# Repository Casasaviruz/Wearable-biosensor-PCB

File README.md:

# Wearable-biosensor-PCB

A battery powered double sided PCB sensor meant to monitor the heart rate, breathing, temperature and sleep and active cycles of lab mice, made as small and non invasive as possible, data is transmitted through Bluetooth

Final Project — CSE 332 (Analog and Digital Circuits), DePaul University,
winter 2026.

# Specifications

- Dimensions: 27mm x 18mm
- Weight: ~ 3.05g (with battery)
- Microcontroller: nRF52832 (ARM Cortex-M4 + radio BLE)
- Sensors: MAX30101 (heart rate/ breathing), TMP117
  (temperature), LSM6DSL (accelerometer/gyroscope)

# Content 
`kicad/` - project files (pcb, schematics, libraries)
`report/` - complete technical report (component reasoning, calculations, simulation results)

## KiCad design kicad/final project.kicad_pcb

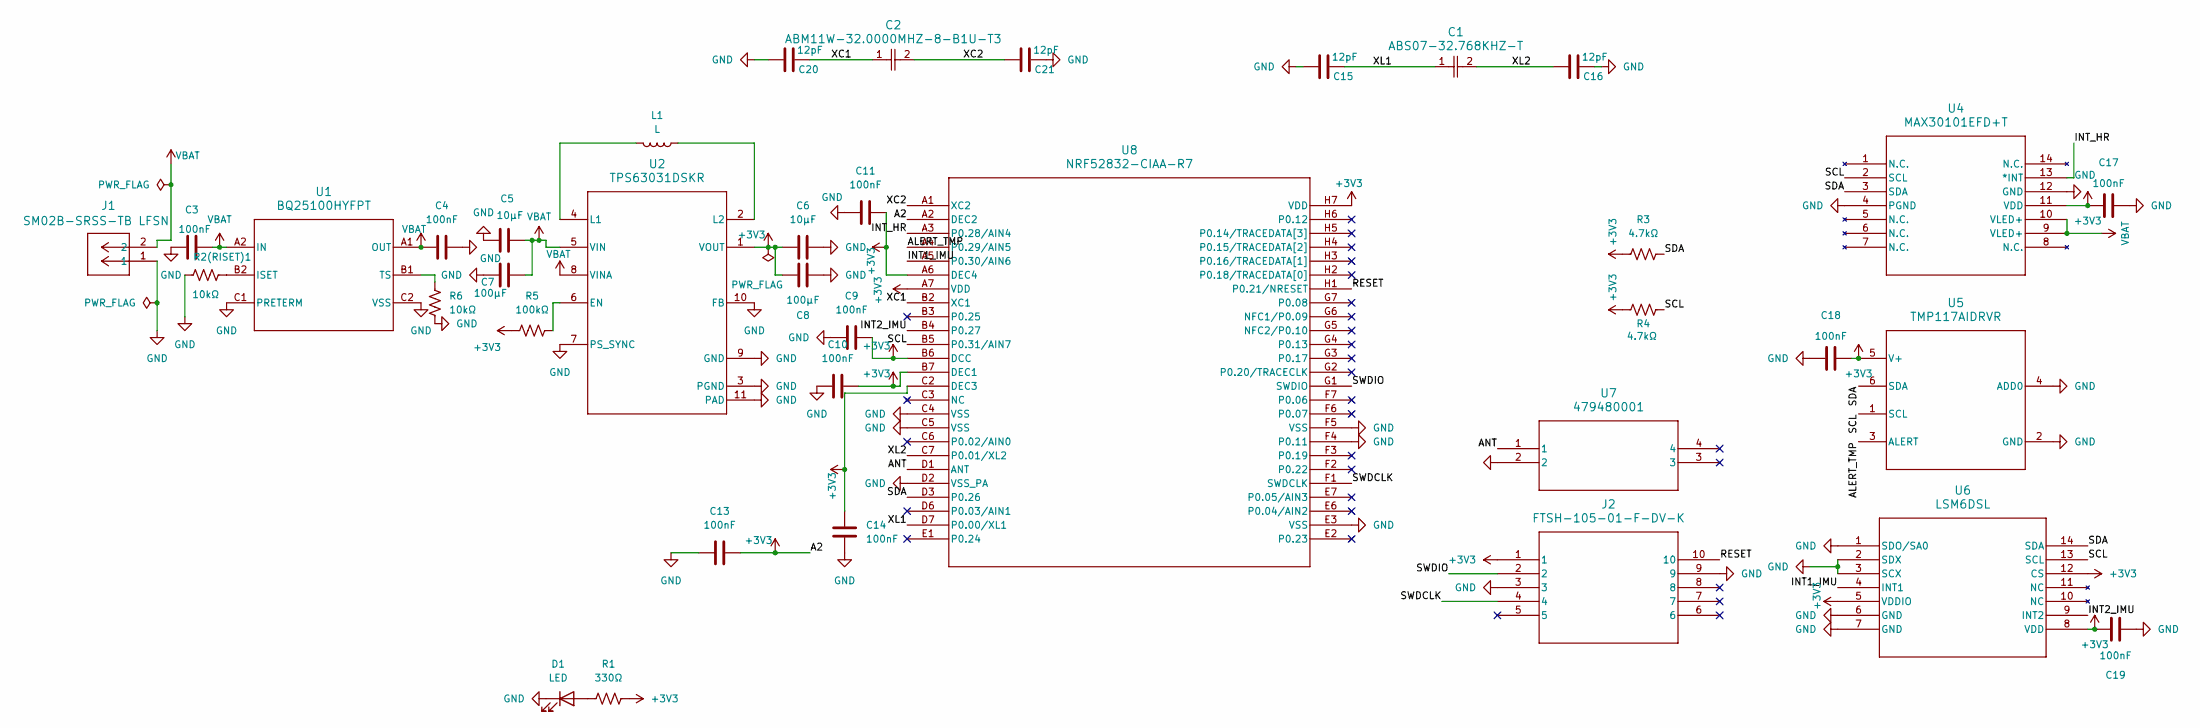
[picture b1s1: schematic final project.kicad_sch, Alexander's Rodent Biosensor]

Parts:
C1: ABS07-32.768KHZ-T; CAP_ABS07-32.768KHZ-T_ABR
C2: ABM11W-32.0000MHZ-8-B1U-T3; CAP_ABM11W-32.0000MHZ-8-B1U-T3_ABR
C3, C4, C9, C10, C11, C13, C14, C17, C18, C19: 100nF; C_0402_1005Metric
C5, C6: 10µF; C_0402_1005Metric
C7, C8: 100µF; C_0805_2012Metric
C15, C16, C20, C21: 12pF; C_0402_1005Metric
D1: LED; LED_0402_1005Metric
J1: SM02B-SRSS-TB LFSN; CONN_SM02B-SRSS-TB_JST
J2: FTSH-105-01-F-DV-K; FTSH-105-01-F-DV-K_SAI
L1: L; L_0402_1005Metric
R1: 330Ω; R_0402_1005Metric
R2(RISET)1, R6: 10kΩ; R_0402_1005Metric
R3, R4: 4.7kΩ; R_0402_1005Metric
R5: 100kΩ; R_0402_1005Metric
U1: BQ25100HYFPT; YFP0006AFAV
U2: TPS63031DSKR; DSK0010A
U4: MAX30101EFD+T; 21-1048F_F143A5&plus_1_MXM
U5: TMP117AIDRVR; DRV0006B
U6: LSM6DSL; QFN_6DSLTR_STM
U7: 479480001; ANT_47948-0001_MOL
U8: NRF52832-CIAA-R7; WLCSP50_NRF52832_NOR

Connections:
+3V3: C6.1, C8.1, C9.2, C10.2, C11.2, C13.2, C14.1, C17.1, C18.2, C19.1, J2.1, R1.2, R3.1, R4.2, R5.1, U2.1 (VOUT), U4.11 (VDD), U5.5 (V+), U6.5 (VDDIO), U6.8 (VDD), U6.12 (CS), U8.A2 (DEC2), U8.A6 (DEC4), U8.A7 (VDD), U8.B6 (DCC), U8.B7 (DEC1), U8.C2 (DEC3), U8.H7 (VDD)
/ALERT_TMP: U5.3 (ALERT), U8.A4 (P0.29/AIN5)
/ANT: U7.1, U8.D1 (ANT)
/INT1_IMU: U6.4 (INT1), U8.A5 (P0.30/AIN6)
/INT2_IMU: U6.9 (INT2), U8.B4 (P0.27)
/INT_HR: U4.13 (*INT), U8.A3 (P0.28/AIN4)
/RESET: J2.10, U8.H1 (P0.21/NRESET)
/SCL: R4.1, U4.2 (SCL), U5.1 (SCL), U6.13 (SCL), U8.B5 (P0.31/AIN7)
/SDA: R3.2, U4.3 (SDA), U5.6 (SDA), U6.14 (SDA), U8.D3 (P0.26)
/SWDCLK: J2.4, U8.F1 (SWDCLK)
/SWDIO: J2.2, U8.G1 (SWDIO)
/XC1: C2.1, C20.2, U8.B2 (XC1)
/XC2: C2.2, C21.1, U8.A1 (XC2)
/XL1: C1.1, C15.2, U8.D7 (P0.00/XL1)
/XL2: C1.2, C16.1, U8.C7 (P0.01/XL2)
GND: C3.1, C4.2, C5.1, C6.2, C7.1, C8.2, C9.1, C10.1, C11.1, C13.1, C14.2, C15.1, C16.2, C17.2, C18.1, C19.2, C20.1, C21.2, D1.1 (K), J1.1, J2.3, J2.9, R2(RISET)1.2, R6.1, U1.C1 (PRETERM), U1.C2 (VSS), U2.3 (PGND), U2.7 (PS_SYNC), U2.9 (GND), U2.10 (FB), U2.11 (PAD), U4.4 (PGND), U4.12 (GND), U5.2 (GND), U5.4 (ADD0), U6.1 (SDO/SA0), U6.2 (SDX), U6.3 (SCX), U6.6 (GND), U6.7 (GND), U7.2, U8.C4 (VSS), U8.C5 (VSS), U8.D2 (VSS_PA), U8.E3 (VSS), U8.F4 (P0.11), U8.F5 (VSS); also elsewhere on the board
unnamed: D1.2 (A), R1.1
unnamed 17: R2(RISET)1.1, U1.B2 (ISET); also elsewhere on the board
unnamed: R6.2, U1.B1 (TS)
unnamed: R5.2, U2.6 (EN)
unnamed: L1.2, U2.4 (L1)
unnamed: L1.1, U2.2 (L2)
VBAT: C3.2, C4.1, C5.2, C7.2, J1.2, U1.A1 (OUT), U1.A2 (IN), U2.5 (VIN), U2.8 (VINA), U4.9 (VLED+), U4.10 (VLED+)

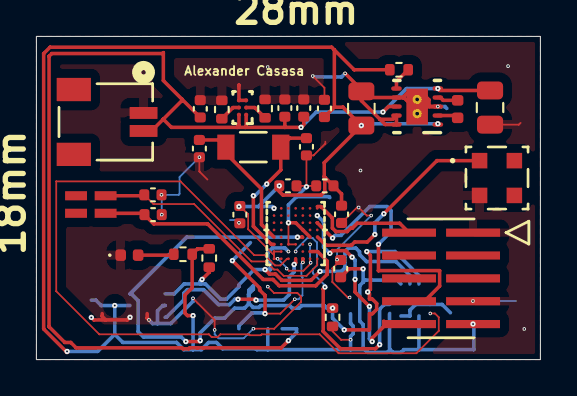
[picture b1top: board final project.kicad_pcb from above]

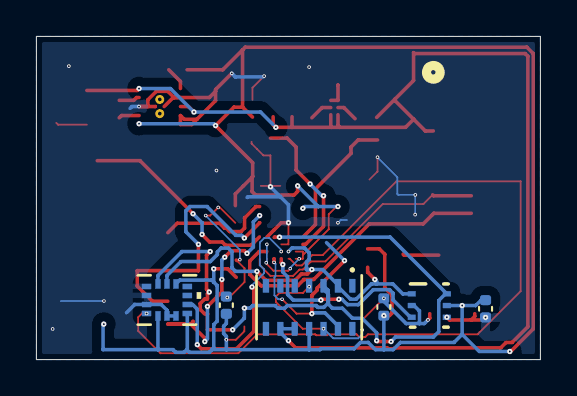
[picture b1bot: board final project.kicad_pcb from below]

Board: 2 copper layers, 28.0 x 18.0 mm, 37 parts (6 on the bottom side), 23 nets.

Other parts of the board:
R2: 10kΩ; R_0402_1005Metric

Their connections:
GND: R2.2; also elsewhere on the board
unnamed 17: R2.1; also elsewhere on the board
